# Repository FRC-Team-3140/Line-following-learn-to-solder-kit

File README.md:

# Line-following-learn-to-solder-kit
Some customized learn to solder kit boards made easier for soldering beginners

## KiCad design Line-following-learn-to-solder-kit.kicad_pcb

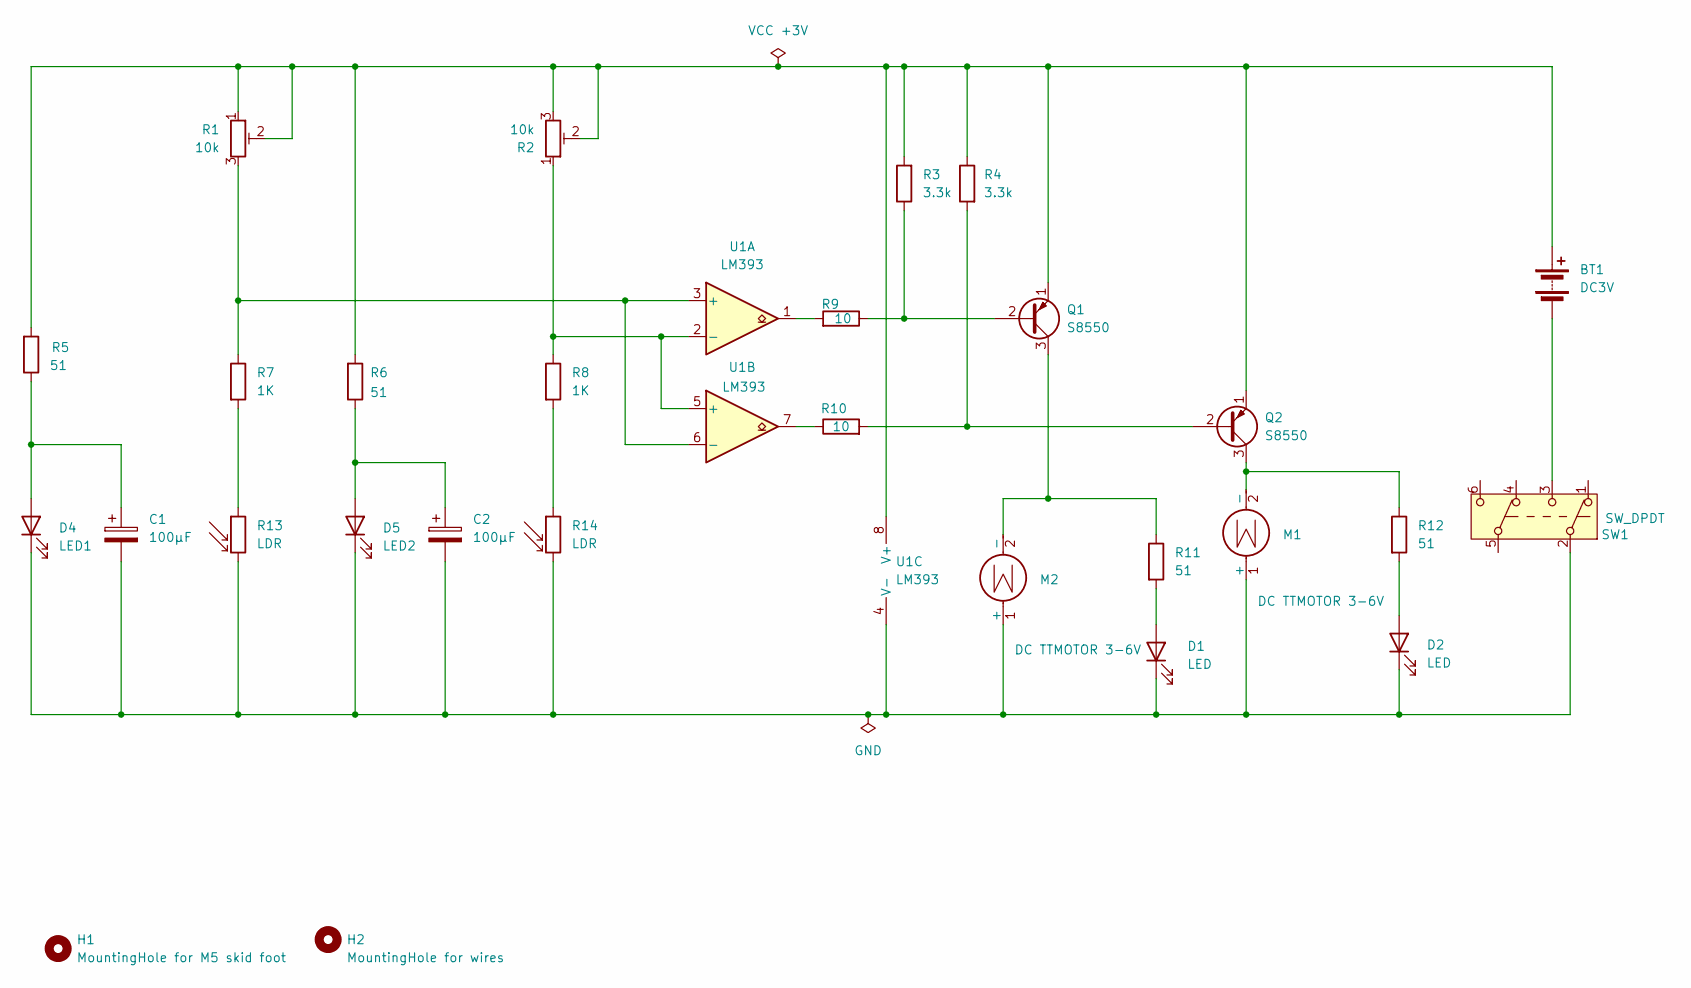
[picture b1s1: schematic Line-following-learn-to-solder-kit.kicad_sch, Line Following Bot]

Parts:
BT1: DC3V; BatteryHolder_Keystone_2462_2xAA
C1, C2: 100μF; CP_Radial_D6.3mm_P2.50mm
D1, D2: LED; LED_D5.0mm
D4: LED1; LED_D5.0mm_Clear
D5: LED2; LED_D5.0mm_Clear
H1: MountingHole for M5 skid foot; MountingHole_5mm_Pad_TopBottom
H2: MountingHole for wires; MountingHole_3mm
M1: DC TTMOTOR 3-6V; TT-Motor
M2: DC TTMOTOR 3-6V; TT-Motor-mirrored
Q1, Q2: S8550; TO-92_HandSolder
R1, R2: 10k; Potentiometer_Runtron_RM-065_Vertical_hand_soldering
R3, R4: 3.3k; R_Axial_DIN0207_L6.3mm_D2.5mm_P7.62mm_Horizontal_hand_solde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
R5, R6, R11, R12: 51; R_Axial_DIN0207_L6.3mm_D2.5mm_P7.62mm_Horizontal_hand_solde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
R7, R8: 1K; R_Axial_DIN0207_L6.3mm_D2.5mm_P7.62mm_Horizontal_hand_solde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
R9, R10: 10; R_Axial_DIN0207_L6.3mm_D2.5mm_P7.62mm_Horizontal_hand_solde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
R13, R14: LDR; R_LDR_5.1x4.3mm_P3.4mm_Vertical_hand_soldering
SW1: SW_DPDT; MHPS2283
U1: LM393; DIP-8_W7.62mm_Socket_LongPads

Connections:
unnamed: BT1.1 (+), Q1.1 (E), Q2.1 (E), R1.1, R1.2, R2.2, R2.3, R3.2, R4.1, R5.2, R6.2, U1.8 (V+)
unnamed: BT1.2 (-), SW1.3 (C)
unnamed: D1.2 (A), R11.2
unnamed: C1.2, C2.2, D1.1 (K), D2.1 (K), D4.1 (K), D5.1 (K), M1.1 (+), M2.1 (+), R13.2, R14.2, SW1.2 (B), U1.4 (V-)
unnamed: D2.2 (A), R12.2
unnamed: C1.1, D4.2 (A), R5.1
unnamed: C2.1, D5.2 (A), R6.1
unnamed: M1.2 (-), Q2.3 (C), R12.1
unnamed: M2.2 (-), Q1.3 (C), R11.1
unnamed: Q1.2 (B), R3.1, R9.1
unnamed: Q2.2 (B), R4.2, R10.2
unnamed: R9.2, U1.1
unnamed: R10.1, U1.7
unnamed: R7.2, R13.1
unnamed: R8.2, R14.1
unnamed: R1.3, R7.1, U1.3 (+), U1.6 (-)
unnamed: R2.1, R8.1, U1.2 (-), U1.5 (+)

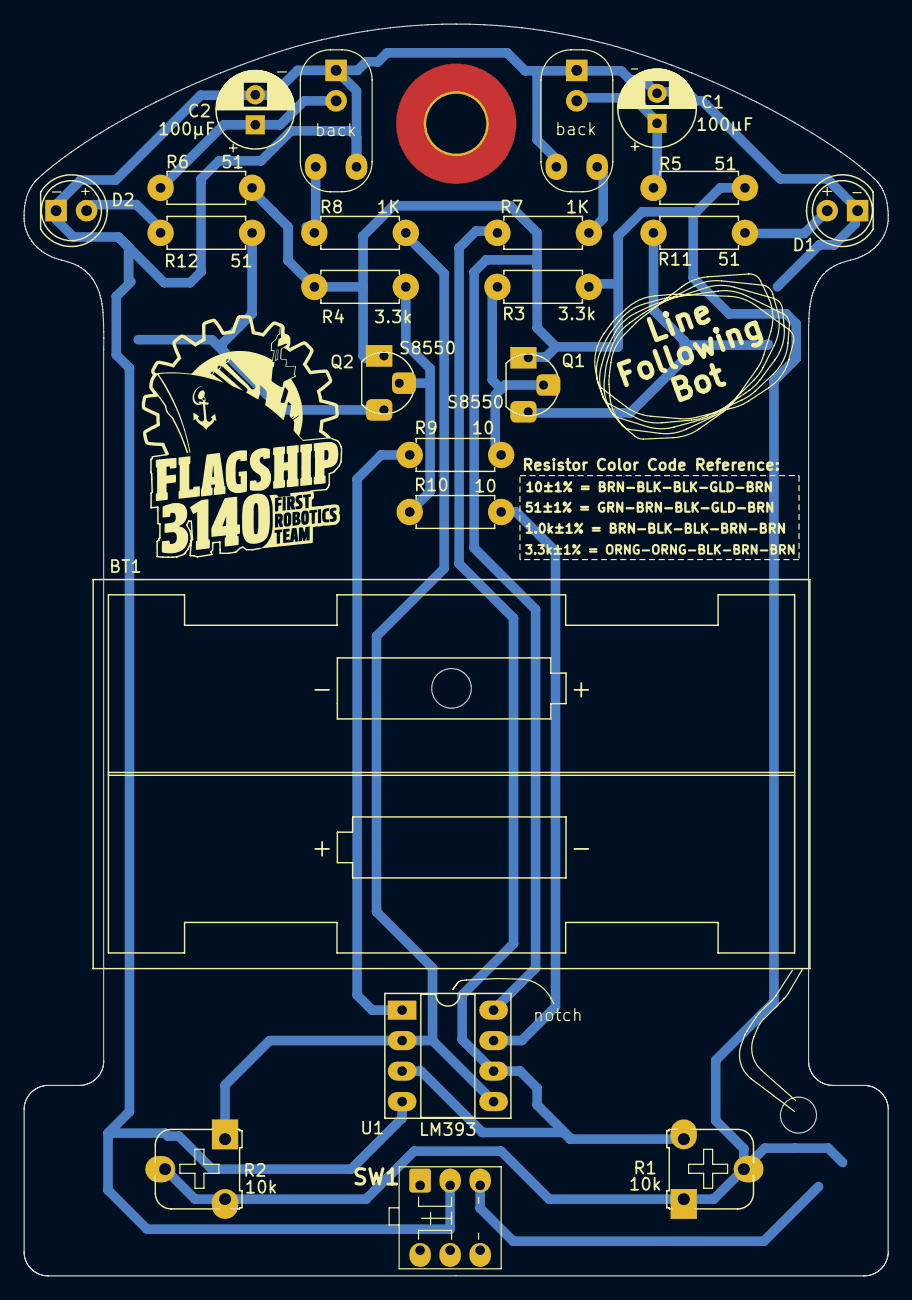
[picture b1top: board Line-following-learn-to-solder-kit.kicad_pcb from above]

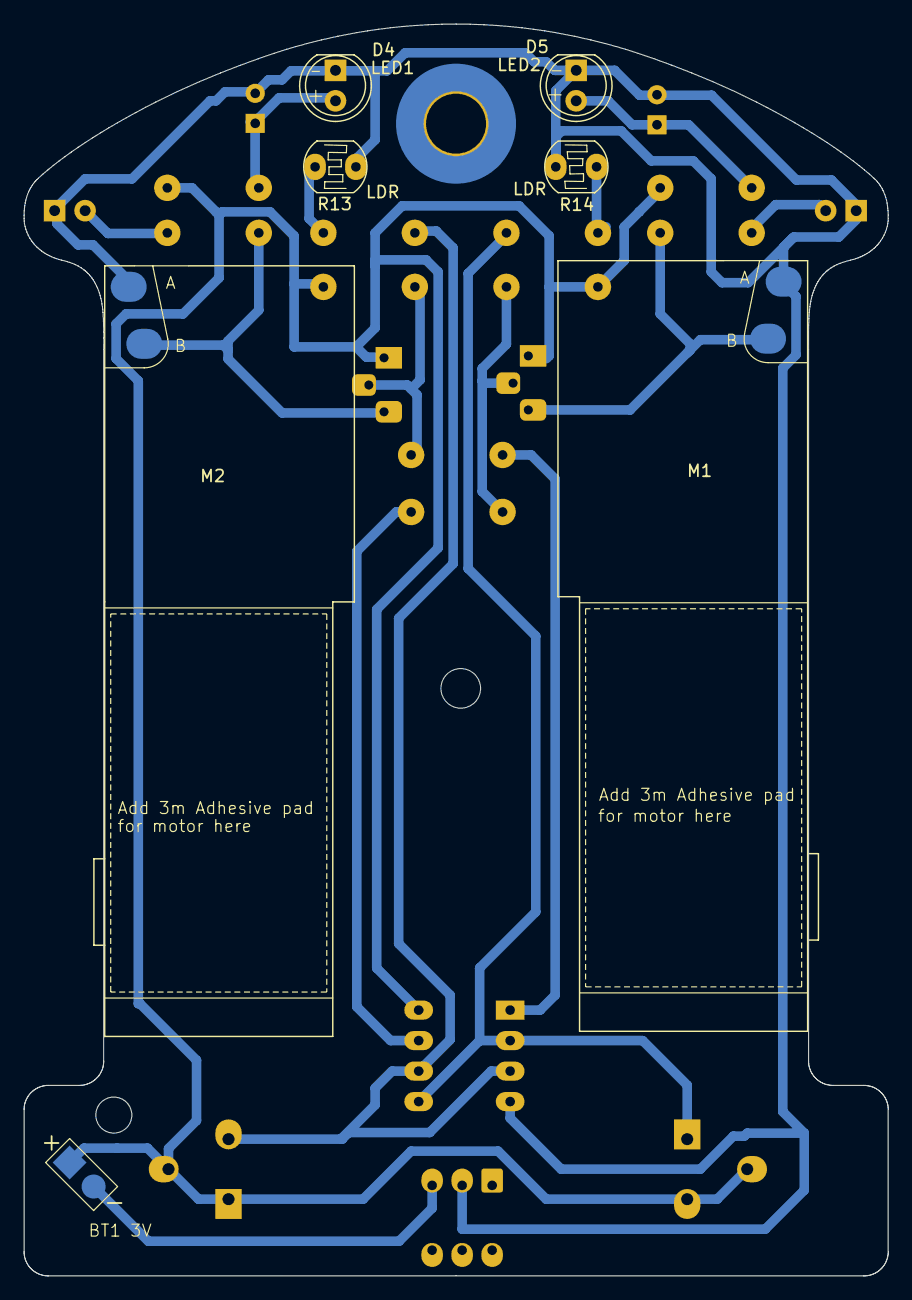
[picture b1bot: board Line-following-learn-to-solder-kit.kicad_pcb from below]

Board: 2 copper layers, 72.0 x 104.3 mm, 29 parts (6 on the bottom side), 17 nets.

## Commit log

2024-05-16 WIP, almost done
2024-05-30 v0.0 release. Still missing some 3d models, exact part number associations.
